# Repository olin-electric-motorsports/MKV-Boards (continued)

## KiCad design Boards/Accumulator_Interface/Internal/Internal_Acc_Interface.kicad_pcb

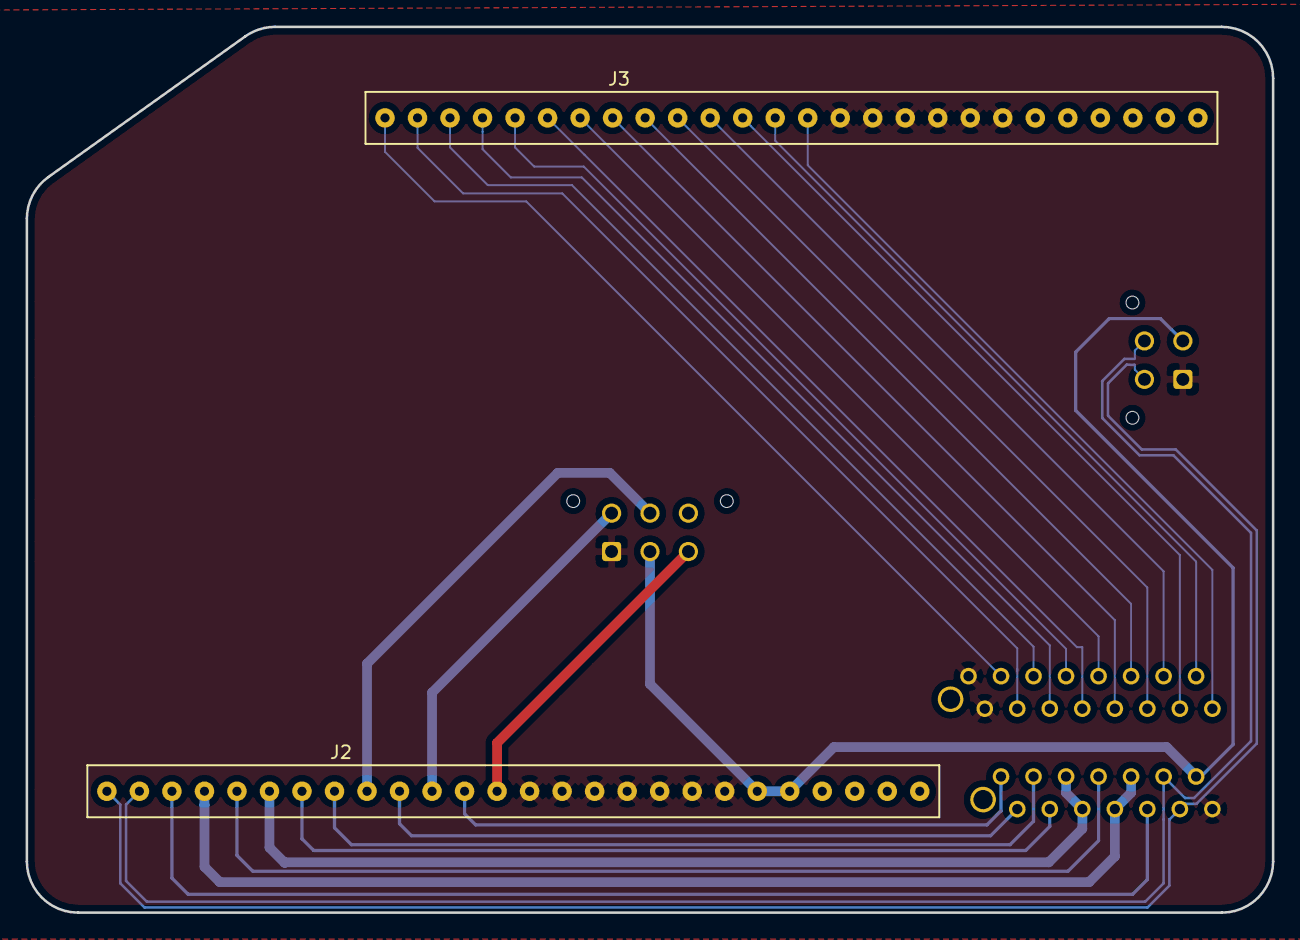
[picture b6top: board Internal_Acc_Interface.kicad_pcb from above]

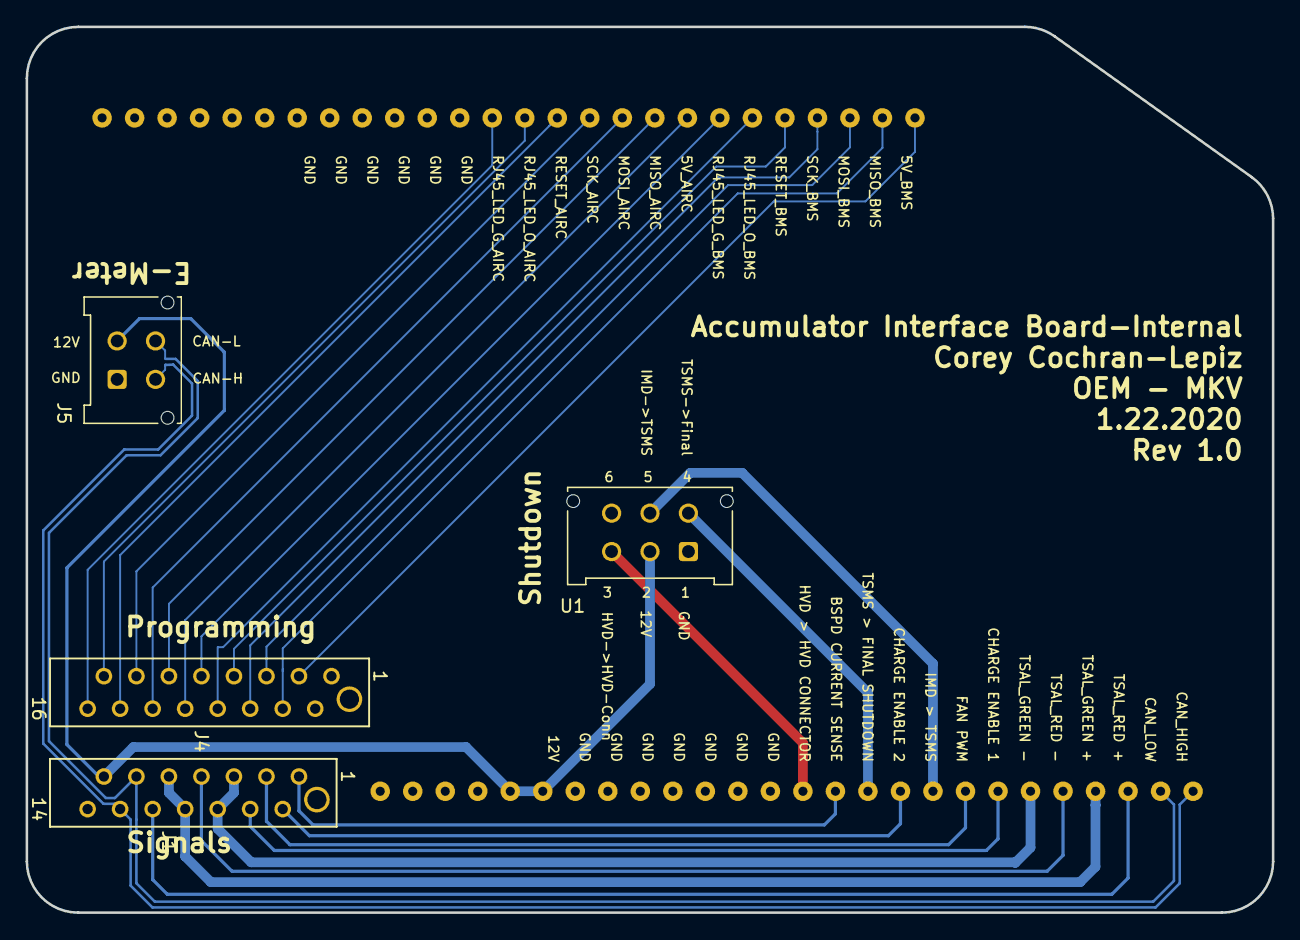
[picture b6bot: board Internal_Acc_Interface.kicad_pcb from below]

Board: 2 copper layers, 97.4 x 69.2 mm, 6 parts (4 on the bottom side), 29 nets.

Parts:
J1: MM_F_VT_14; micromatch_female_vert_14
J2: SS-126-G-2; 26pos_screwsocket_.1in
J3: BBS-126-G-A; 26pos_screwsocket_.1in
J4: MM_F_VT_16; micromatch_female_vert_16
J5: MicroFit_VT_4
U1: MicroFit_VT_6

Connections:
/5V_AIRC: J3.8, J4.10
/5V_BMS: J3.1, J4.3
/12V: J1.13, J2.21, J2.22, J5.2, U1.2
/BSDP-Current-Sense: J1.1, J2.12
/CAN_N: J1.11, J2.2, J5.4
/CAN_P: J1.12, J2.1, J5.3
/ChargeEnable1: J1.4, J2.7
/ChargeEnable2: J1.2, J2.10
/FAN-PWM: J1.3, J2.8
/GND: J1.14, J2.14, J2.15, J2.16, J2.17, J2.18, J2.19, J2.20, J3.15, J3.16, J3.17, J3.18, J3.19, J3.20, J4.1, J4.2, J5.1, U1.1
/HVD->HVD-Connector: J2.13, U1.3
/IMD->TSMS: J2.9, U1.5
/LED_G_AIRC: J3.14, J4.16
/LED_G_BMS: J3.7, J4.9
/LED_O_AIRC: J3.13, J4.15
/LED_O_BMS: J3.6, J4.8
/MISO_AIRC: J3.9, J4.11
/MISO_BMS: J3.2, J4.4
/MOSI_AIRC: J3.10, J4.12
/MOSI_BMS: J3.3, J4.5
/RESET_AIRC: J3.12, J4.14
/RESET_BMS: J3.5, J4.7
/SCK_AIRC: J3.11, J4.13
/SCK_BMS: J3.4, J4.6
/TSAL-Green-Neg: J1.5, J1.6, J2.6
/TSAL-Green-Pos: J1.8, J1.9, J2.4
/TSAL-Red-Neg: J1.7, J2.5
/TSAL-Red-Pos: J1.10, J2.3
/TSMS->FinalShutdown: J2.11, U1.4

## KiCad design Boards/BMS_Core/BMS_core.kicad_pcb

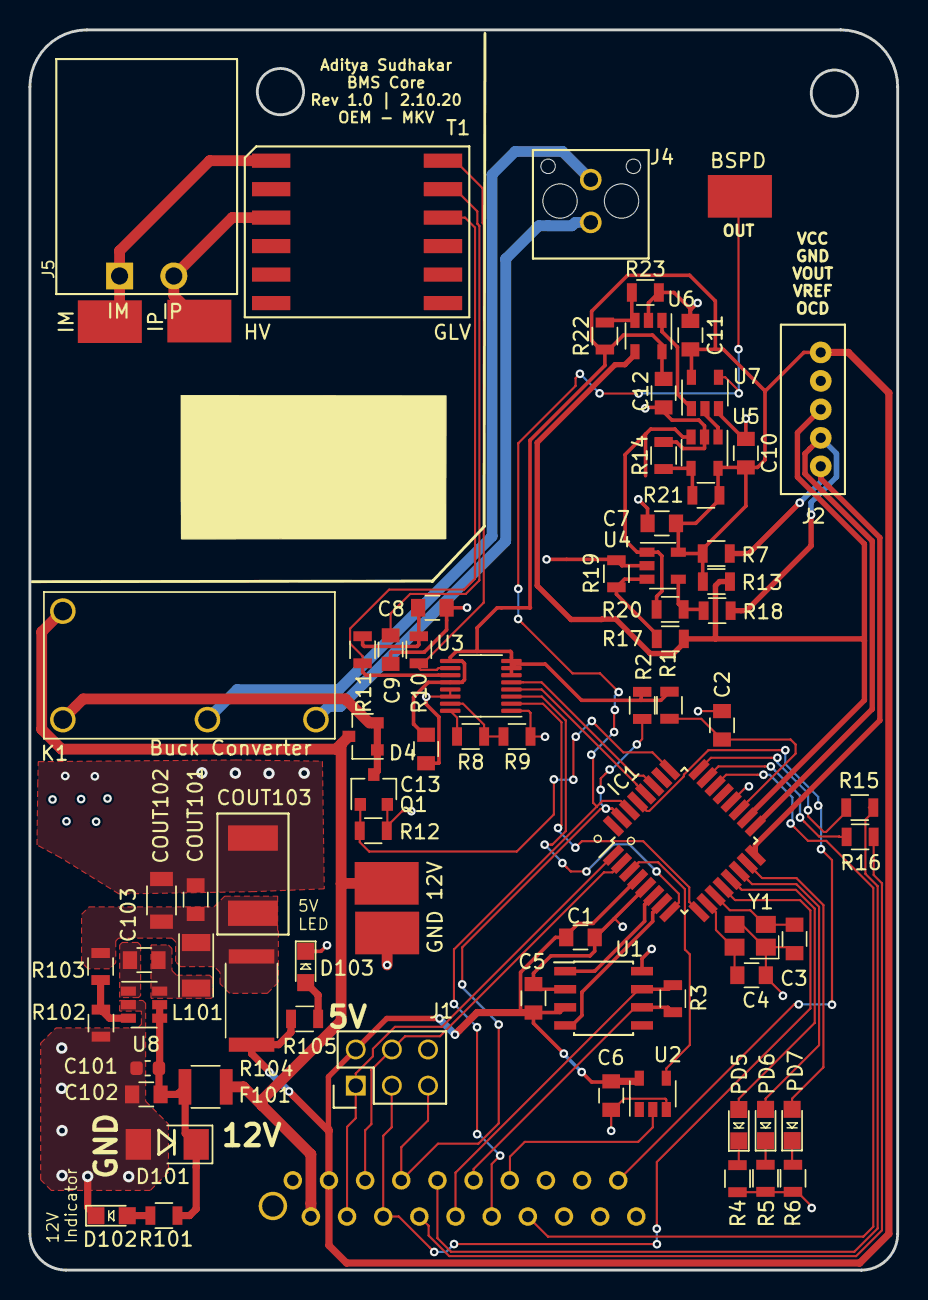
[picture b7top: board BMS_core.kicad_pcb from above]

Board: 2 copper layers, 61.0 x 87.1 mm, 79 parts (1 on the bottom side), 62 nets.

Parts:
12V: Test_Point_SMD
BSPD: Test_Point_SMD
C1, C5, C6, C7, C10, C11, C12, C13, C102, C103: C_0.1uF; C_0805_OEM
C2: C_100pF; C_0805_OEM
C3, C4: C_30pF; C_0805_OEM
C8, C9: C_10nF; C_0805_OEM
C101: C_2.2uF; C_0603_1608Metric
COUT101: C_47uF; C_0805_OEM
COUT102: C_22uF; C_1206_OEM
COUT103: C_33uF; Fuse_1812
D4: BAS40-00; SOT-23
D101: D_Zener_18V; DO-214AA
D102, D103: LED_0805; LED_0805_OEM
F101: 500mA; Fuse_1210
GND: Test_Point_SMD
IC1: ATMEGA16M1; TQFP-32_7x7mm_Pitch0.8mm
IM: Test_Point_SMD
IP: Test_Point_SMD
J1: CONN_02X03; Pin_Header_Straight_2x03
J2: B5B-PH-K-S
J3: MM_F_VT_20; micromatch_female_vert_20
J4: MicroFit_V_2
J5: isoSPI-Cutout; iso_spi_cutout
K1: G5Q-1A4-DC12; Relay_SPST_OMRON-G5Q-1A4_OEM
L101: L_100uH; L_100uH_OEM
PD5, PD6, PD7: LED_0805; LED_0805_OEM
Q1: SSM3K333R; SOT-23F
R1: R_100; R_0805_OEM
R2, R7, R12, R13, R17, R18, R19, R20, R22: R_10K; R_0805_OEM
R3, R4, R5, R6, R15, R16, R105: R_200; R_0805_OEM
R8, R9, R23, R101: R_1K; R_0805_OEM
R10, R11: R_60.4; R_0805_OEM
R14: R_1K_0.1; R_0805_OEM
R21: R_14.3K; R_0805_OEM
R102: R_25K; R_0805_OEM
R103: R_100K; R_0805_OEM
R104: R_0_2512; R_2512_OEM
T1: T_LAN_SM91501ALE
U1: MCP2561-E_SN; SOIC-8_3.9x4.9mm_Pitch1.27mm_OEM
U2: SN74LVC1G17; SOT-23-5
U3: LTC6820HMS; MSOP-16_3x4mm_P0.5mm
U4, U5, U6: MCP6001; SOT-23-5_OEM
U7: SN74LVC1G32; SOT-23-5_OEM
U8: TPS560430YF; SOT-23-6_OEM
Y1: Crystal_SMD; Crystal_SMD_FA238

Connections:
+12V: 12V.1, D4.3, F101.1, J3.2, K1.5
/BMS_SENSE: IC1.22, J3.14
/BSPD_CURRENT: BSPD.1, IC1.30, J3.12, U7.4
/CANH: J3.10, R3.1, U1.7
/CANL: J3.11, R3.2, U1.6
/CHARGE_ENABLE1: IC1.29, J3.19
/CS_iso: IC1.27, U3.5
/FAN_PWM: J3.13, U2.2
/FAN_PWM_RAW: IC1.3, U2.4
/IM: IM.1, J5.1, T1.1
/IP: IP.1, J5.2, T1.3
/MISO: IC1.1, J1.1, J3.4
/MISO_iso: IC1.8, U3.3
/MOSI: IC1.2, J1.4, J3.5
/MOSI_iso: IC1.9, U3.2
/PROG_1: IC1.13, PD5.2
/PROG_2: IC1.14, PD6.2
/PROG_3: IC1.15, PD7.2
/RELAY_DRIVE: IC1.25, Q1.1, R12.2
/RESET: IC1.31, J1.5, J3.7, R2.2
/RJ45_LED1: J3.8, R16.1
/RJ45_LED2: J3.9, R15.1
/RXCAN: IC1.7, U1.4
/SCK: IC1.12, J1.3, J3.6
/SCK_iso: IC1.28, U3.4
/SHDN_IN(MAIN_PACK->BMS): J4.1, K1.3
/SHDN_OUT(BMS->IMD): J4.2, K1.2
/TXCAN: IC1.6, U1.1
/VOUT: IC1.18, J2.3, R13.1, R17.1, U6.4
/VREF: IC1.17, J2.4, R18.1
/~OCD: IC1.16, J2.5, R7.2
GND: C1.2, C2.2, C3.2, C4.2, C5.2, C6.1, C7.2, C8.2, C9.2, C10.2, C11.2, C12.2, C13.2, C101.2, C102.2, COUT101.2, COUT102.2, COUT103.2, D101.2, D102.1, D103.1, GND.1, IC1.5, IC1.20, J1.6, J2.2, J3.1, J3.15, J3.16, J3.17, J3.18, J3.20, J3.21, Q1.2, R4.2, R5.2, R6.2, R9.2, R12.1, R14.2, R19.1, R23.2, R102.2, U1.2, U1.8, U2.3, U3.1, U3.13, U3.14, U4.2, U5.2, U6.2, U7.3, U8.2, Y1.2, Y1.4
unnamed: C2.1, IC1.19, R1.2
unnamed: C3.1, IC1.11, Y1.1
unnamed: C4.1, IC1.10, Y1.3
unnamed: C8.1, R10.2, R11.1
unnamed: C9.1, T1.11
unnamed: C101.1, C102.1, D101.1, F101.2, R101.1, U8.4, U8.5
unnamed: C103.1, L101.1, U8.6
unnamed: C103.2, U8.1
unnamed: COUT101.1, COUT102.1, COUT103.1, L101.2, R103.2, R104.2
unnamed: PD5.1, R4.1
unnamed: PD6.1, R5.1
unnamed: PD7.1, R6.1
unnamed: D4.1, D4.2, K1.1, Q1.3
unnamed: D102.2, R101.2
unnamed: D103.2, R105.2
unnamed: IC1.23, R16.2
unnamed: IC1.24, R15.2
unnamed: R8.1, U3.16
unnamed: R8.2, R9.1, U3.15
unnamed: R10.1, T1.12, U3.10
unnamed: R11.2, T1.10, U3.11
unnamed: R14.1, R21.1, U5.4
unnamed: R17.2, R19.2, U4.3
unnamed: R18.2, R20.1, U4.4
unnamed: R20.2, U4.1, U5.3
unnamed: R22.2, R23.1, U6.3
unnamed: R102.1, R103.1, U8.3
unnamed: U5.1, U7.2
unnamed: U6.1, U7.1
VCC: C1.1, C5.1, C6.2, C7.1, C10.1, C11.1, C12.1, C13.1, IC1.4, J1.2, J2.1, J3.3, R1.1, R2.1, R7.1, R13.2, R21.2, R22.1, R104.1, R105.1, U1.3, U2.5, U3.6, U3.7, U3.8, U3.9, U3.12, U4.5, U5.5, U6.5, U7.5
